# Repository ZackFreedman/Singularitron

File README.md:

# Singularitron
## Ridiculous VFD-equipped modular cyberwatch

More info at the [Singularitron's Hackaday.io page.](https://hackaday.io/project/169343-singularitron-modular-cyberwatch)

The Singularitron is a massive wrist-mounted wearable device with four expansion slots. Equip any combination of flashlight, laser, IR thermometer, environmental, and SD card modules, and stun the crowd with RGB buttons. The ultra-bright, extremely breakable VFD adds bright-daylight readability... and style.

Real talk, this does work, but is not intended to be a serious project. A VFD is a terrible choice for a wearable, and many parts of the project are suboptimal, ridiculous, and/or barely functional. Also, I made a bunch of boo-boos on the board and fixed them with airwires. I'll fix that some time, maybe.

That said, it serves its purpose - drawing attention at Meetups and conferences - really well. The cartridge form-factor is pretty cool, and this has neat super-small implementations of some interesting parts. Have fun!

If you really do want to build this, there are a lot of gotchas:

* I'll add them
* Eventually
* Right here

Copyright 2017 Zack Freedman

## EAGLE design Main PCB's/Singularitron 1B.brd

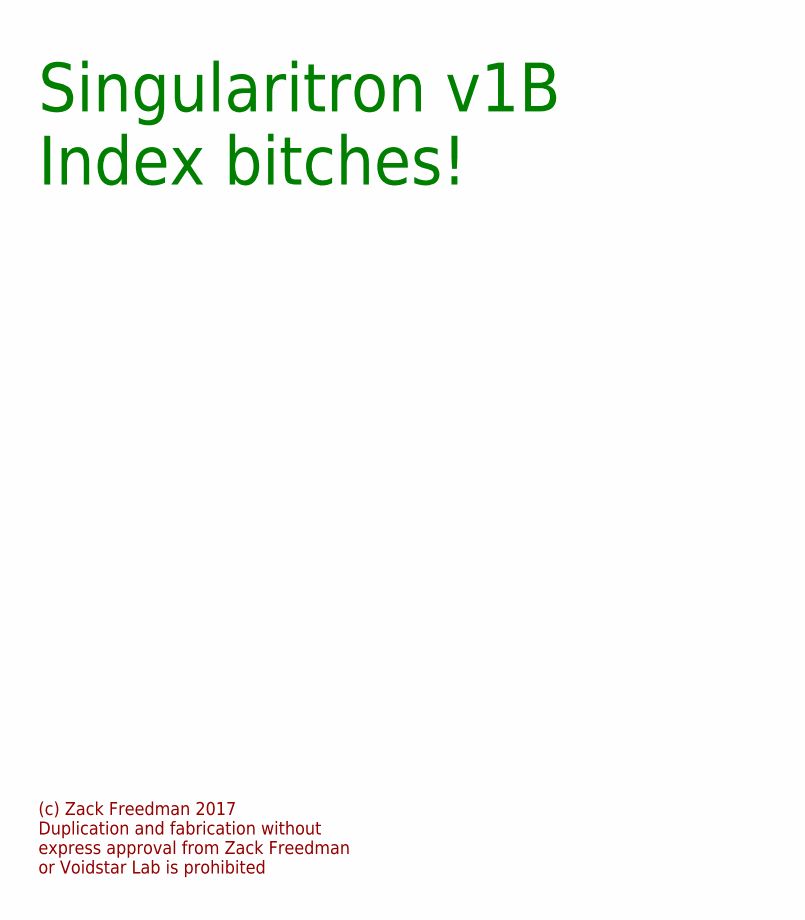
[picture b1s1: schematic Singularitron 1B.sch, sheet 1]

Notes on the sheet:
Singularitron v1B Index bitches!
(c) Zack Freedman 2017 Duplication and fabrication without express approval from Zack Freedman or Voidstar Lab is prohibited

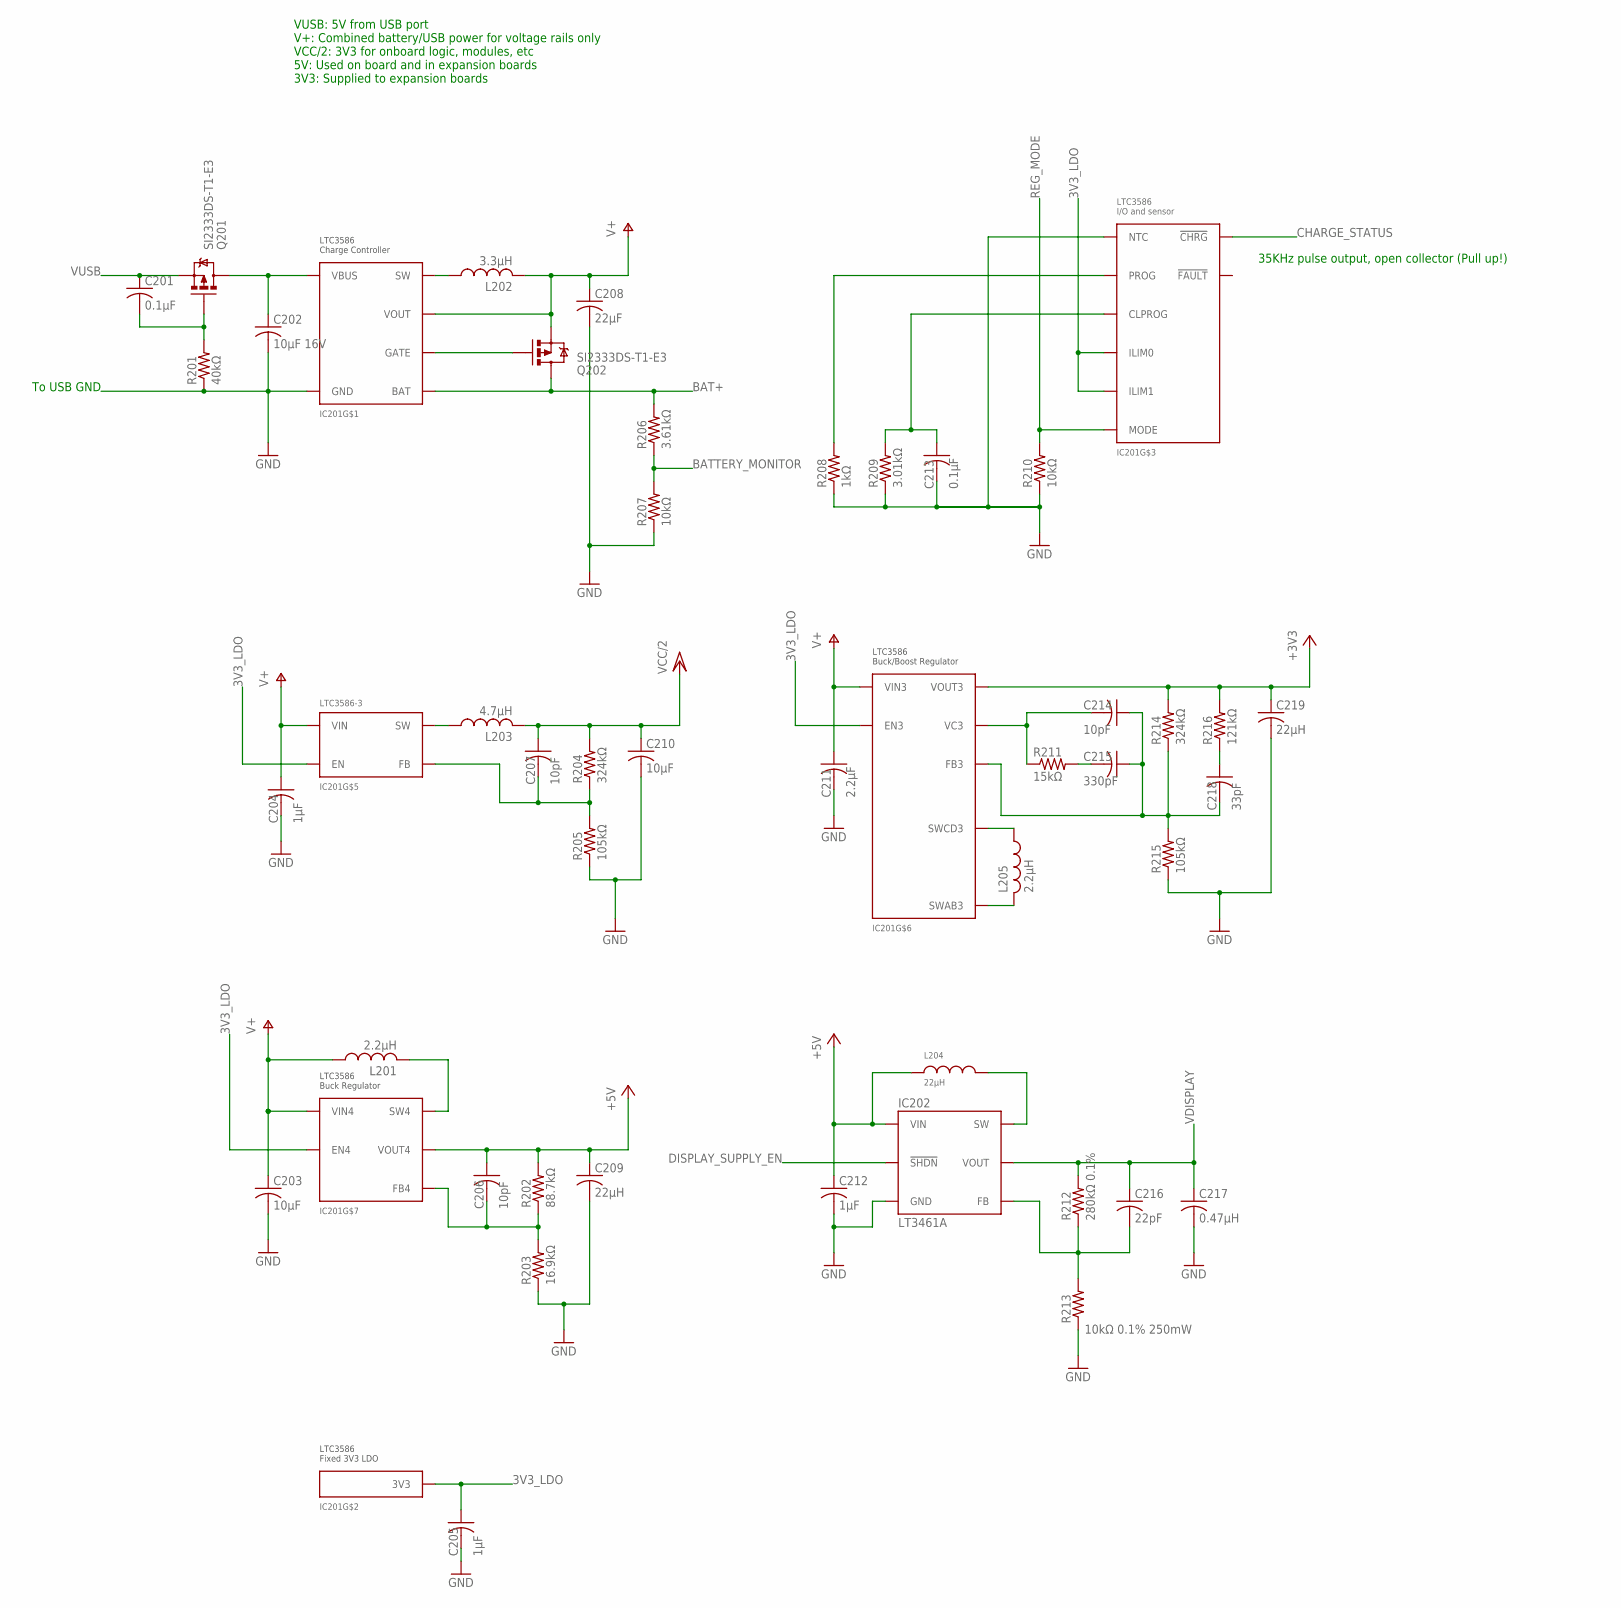
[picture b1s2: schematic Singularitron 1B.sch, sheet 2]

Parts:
C201, C213: 0.1µF; C0603
C202: 10µF 16V; C0805
C203, C210: 10µF; C0805
C204, C205: 1µF; C0603
C206, C207, C214: 10pF; C0603
C208: 22µF; C1210
C209, C219: 22µH; C1210
C211: 2.2µF; C0603
C212: 1µF; C0805
C215: 330pF; C0603
C216: 22pF; C0805
C217: 0.47µH; C1210
C218: 33pF; C0603
IC201: LTC3586-3; QFN-38_EP_UFE
IC202: LT3461A; SOT-23
L201, L205: 2.2µH; CDRH4D22/HP
L202: 3.3µH; CDRH6D12
L203: 4.7µH; CDRH3D16/HP
L204: 22µH; CDPH4D19F
Q201, Q202: SI2333DS-T1-E3; SOT23-3
R201: 40kΩ; R0603
R202: 88.7kΩ; R0603
R203: 16.9kΩ; R0603
R204, R214: 324kΩ; R0603
R205, R215: 105kΩ; R0603
R206: 3.61kΩ; R0603
R207, R210: 10kΩ; R0603
R208: 1kΩ; R0603
R209: 3.01kΩ; R0603
R211: 15kΩ; R0603
R212: 280kΩ 0.1%; R0603
R213: 10kΩ 0.1% 250mW; R0805
R216: 121kΩ; R0603

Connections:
3V3_LDO: C205.1, IC201.P$1 (ILIM0), IC201.P$2 (ILIM1), IC201.P$3 (3V3), IC201.P$18 (EN3), IC201.P$20 (EN), IC201.P$33 (EN4); also elsewhere on the board
+3V3: C219.1, IC201.P$16 (VOUT3), IC201.P$17 (VOUT3), R214.2, R216.2; also elsewhere on the board
+5V: C206.1, C209.1, C212.1, IC201.P$6 (VOUT4), IC201.P$7 (VOUT4), IC202.P6 (VIN), L204.P$1, R202.2; also elsewhere on the board
BAT+: IC201.P$32 (BAT), Q202.3 (D), R206.2; also elsewhere on the board
BATTERY_MONITOR: R206.1, R207.2; also elsewhere on the board
CHARGE_STATUS: IC201.P$30 (!CHRG); also elsewhere on the board
CLPROG: C213.1, IC201.P$4 (CLPROG), R209.2
DISPLAY_SUPPLY_EN: IC202.P4 (!SHDN); also elsewhere on the board
GND: C202.2, C203.2, C204.2, C205.2, C208.2, C209.2, C210.2, C211.2, C212.2, C213.2, C217.2, C219.2, IC201.EP (GND), IC201.P$5 (NTC), IC202.P2 (GND), R201.1, R203.1, R205.1, R207.1, R208.1, R209.1, R210.1, R213.1, R215.1; also elsewhere on the board
unnamed: C202.1, IC201.P$35 (VBUS), IC201.P$36 (VBUS), Q201.3 (D)
unnamed: IC201.P$37 (SW), L202.P$1 (1)
unnamed: C201.2, Q201.1 (G), R201.2
unnamed: IC201.P$31 (GATE), Q202.1 (G)
unnamed: IC201.P$25 (SW), L203.P$1 (1)
unnamed: IC201.P$29 (PROG), R208.2
unnamed: C207.2, IC201.P$23 (FB), R204.1, R205.2
unnamed: IC202.P1 (SW), L204.P$2
unnamed: C214.2, IC201.P$12 (VC3), R211.1
unnamed: C216.2, IC202.P3 (FB), R212.1, R213.2
unnamed: C215.2, R211.2
unnamed: IC201.P$8 (SW4), L201.P$2 (2)
unnamed: C218.1, R216.1
unnamed: C206.2, IC201.P$10 (FB4), R202.1, R203.2
unnamed: C214.1, C215.1, C218.2, IC201.P$11 (FB3), R214.1, R215.2
unnamed: IC201.P$19 (SWCD3), L205.P$1 (1)
unnamed: IC201.P$13 (SWAB3), L205.P$2 (2)
REG_MODE: IC201.P$9 (MODE), R210.2
V+: C203.1, C204.1, C208.1, C211.1, IC201.P$14 (VIN3), IC201.P$15 (VIN3), IC201.P$22 (VIN4), IC201.P$24 (VIN), IC201.P$34 (VOUT), L201.P$1 (1), L202.P$3 (2), Q202.2 (S)
VCC/2: C207.1, C210.1, L203.P$2 (2), R204.2; also elsewhere on the board
VDISPLAY: C216.1, C217.1, IC202.P5 (VOUT), R212.2; also elsewhere on the board
VUSB: C201.1, Q201.2 (S); also elsewhere on the board

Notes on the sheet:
To USB GND
VUSB: 5V from USB port V+: Combined battery/USB power for voltage rails only VCC/2: 3V3 for onboard logic, modules, etc 5V: Used on board and in expansion boards 3V3: Supplied to expansion boards
35KHz pulse output, open collector (Pull up!)

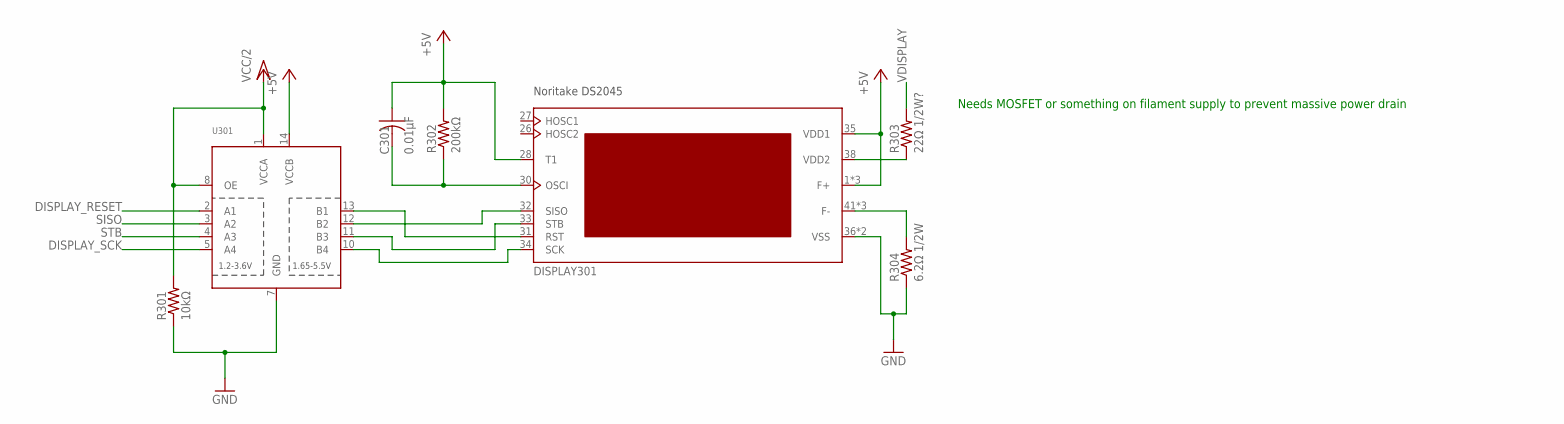
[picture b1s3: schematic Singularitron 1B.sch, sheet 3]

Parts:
C301: 0.01µF; C0603
DISPLAY301: DS2045
R301: 10kΩ; R0603
R302: 200kΩ; R0603
R303: 22Ω 1/2W?; R0805
R304: 6.2Ω 1/2W; R0805
U301: TXB0104PWR; TSSOP14

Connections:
+5V: C301.1, DISPLAY301.1 (F+), DISPLAY301.2 (F+), DISPLAY301.3 (F+), DISPLAY301.28 (T1), DISPLAY301.35 (VDD1), R302.2, U301.14 (VCCB); also elsewhere on the board
DISPLAY_RESET: U301.2 (A1); also elsewhere on the board
DISPLAY_SCK: U301.5 (A4); also elsewhere on the board
GND: DISPLAY301.36 (VSS), DISPLAY301.37 (VSS), R301.1, R304.1, U301.7 (GND); also elsewhere on the board
unnamed: DISPLAY301.31 (RST), U301.13 (B1)
unnamed: DISPLAY301.38 (VDD2), R303.1
unnamed: DISPLAY301.41 (F-), DISPLAY301.42 (F-), DISPLAY301.43 (F-), R304.2
unnamed: DISPLAY301.32 (SISO), U301.12 (B2)
unnamed: DISPLAY301.33 (STB), U301.11 (B3)
unnamed: DISPLAY301.34 (SCK), U301.10 (B4)
unnamed: C301.2, DISPLAY301.30 (OSCI), R302.1
SISO: U301.3 (A2); also elsewhere on the board
STB: U301.4 (A3); also elsewhere on the board
VCC/2: R301.2, U301.1 (VCCA), U301.8 (OE); also elsewhere on the board
VDISPLAY: R303.2; also elsewhere on the board

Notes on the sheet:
Needs MOSFET or something on filament supply to prevent massive power drain

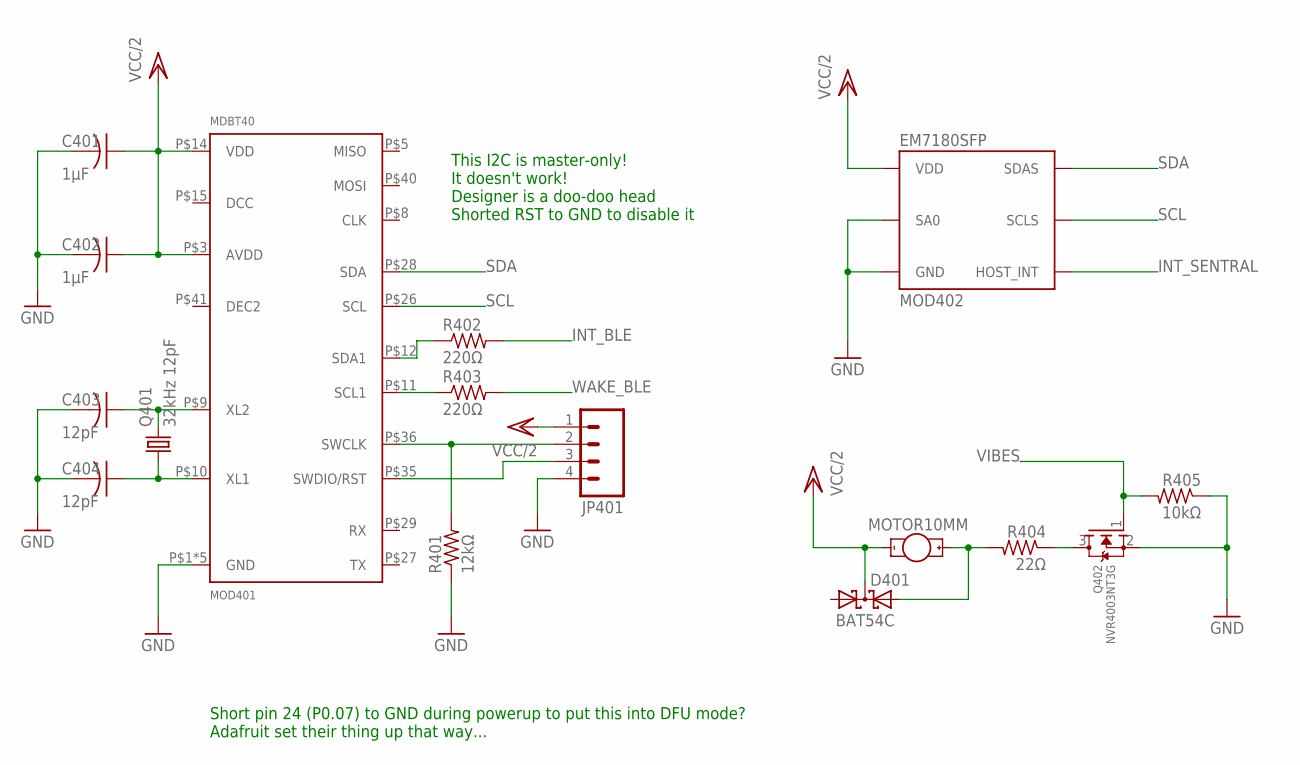
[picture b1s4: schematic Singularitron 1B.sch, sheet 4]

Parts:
C401, C402: 1µF; C0603
C403, C404: 12pF; C0603
D401: BAT54C; SOT23
JP401: M041.27MM; 1X04-1.27MM
MOD401: MDBT40
MOD402: EM7180SFP
MOTOR401: MOTOR10MM; VIBE-MOTOR-10MM
Q401: 32kHz 12pF; FC-12M
Q402: NVR4003NT3G; SOT23
R401: 12kΩ; R0603
R402, R403: 220Ω; R0603
R404: 22Ω; R0603
R405: 10kΩ; R0603

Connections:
GND: C401.2, C402.2, C403.2, C404.2, JP401.4, MOD401.P$1 (GND), MOD401.P$2 (GND), MOD401.P$13 (GND), MOD401.P$25 (GND), MOD401.P$42 (GND), MOD402.P$5 (SA0), MOD402.P$6 (GND), Q402.2 (S), R401.1, R405.1; also elsewhere on the board
INT_BLE: R402.2; also elsewhere on the board
INT_SENTRAL: MOD402.P$4 (HOST_INT); also elsewhere on the board
unnamed: MOD401.P$12 (SDA1), R402.1
unnamed: D401.2 (A2), MOTOR401.+, R404.2
unnamed: MOD401.P$11 (SCL1), R403.1
unnamed: Q402.3 (D), R404.1
unnamed: C404.1, MOD401.P$10 (XL1), Q401.1
unnamed: C403.1, MOD401.P$9 (XL2), Q401.2
unnamed: JP401.2, MOD401.P$36 (SWCLK), R401.2
unnamed: JP401.3, MOD401.P$35 (SWDIO/RST)
SCL: MOD401.P$26 (SCL), MOD402.P$3 (SCLS); also elsewhere on the board
SDA: MOD401.P$28 (SDA), MOD402.P$2 (SDAS); also elsewhere on the board
VCC/2: C401.1, C402.1, D401.3 (CC), JP401.1, MOD401.P$3 (AVDD), MOD401.P$14 (VDD), MOD402.P$1 (VDD), MOTOR401.-; also elsewhere on the board
VIBES: Q402.1 (G), R405.2; also elsewhere on the board
WAKE_BLE: R403.2; also elsewhere on the board

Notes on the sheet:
This I2C is master-only! It doesn't work! Designer is a doo-doo head Shorted RST to GND to disable it
Short pin 24 (P0.07) to GND during powerup to put this into DFU mode? Adafruit set their thing up that way...

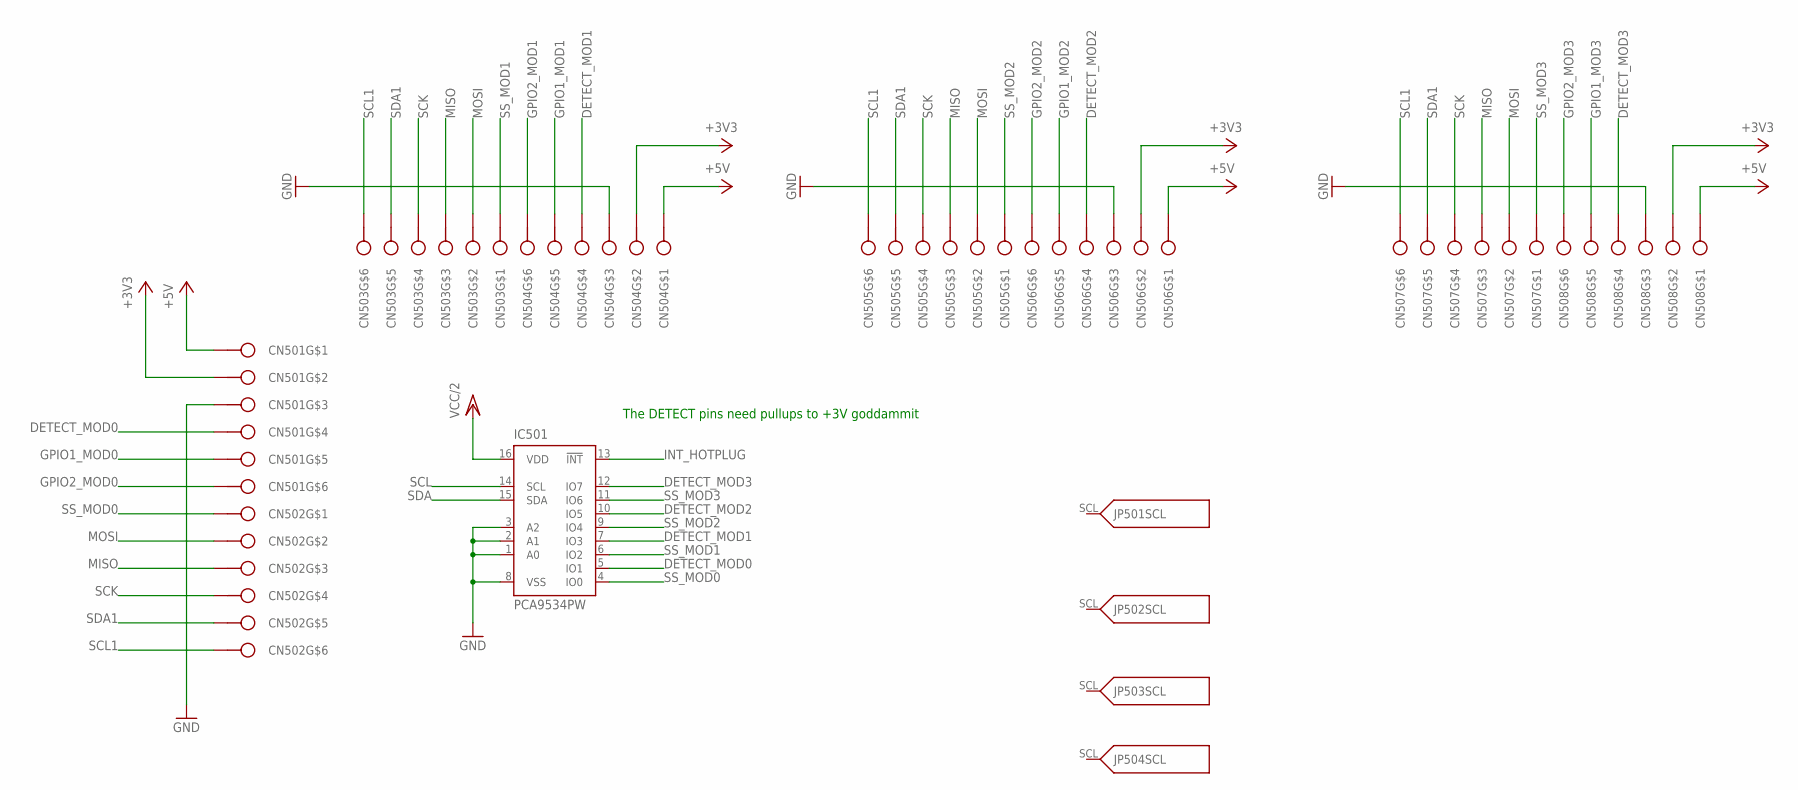
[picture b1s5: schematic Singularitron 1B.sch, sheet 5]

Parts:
CN501, CN502, CN503, CN504, CN505, CN506, CN507, CN508: AVX_9155066; 9155006
IC501: PCA9534PW; TSSOP16
JP501, JP502, JP503, JP504: SINGULARITRON_CART_BASE

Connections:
+3V3: CN501.PAD2, CN504.PAD2, CN506.PAD2, CN508.PAD2; also elsewhere on the board
+5V: CN501.PAD1, CN504.PAD1, CN506.PAD1, CN508.PAD1; also elsewhere on the board
DETECT_MOD0: CN501.PAD4, IC501.5 (IO1)
DETECT_MOD1: CN504.PAD4, IC501.7 (IO3)
DETECT_MOD2: CN506.PAD4, IC501.10 (IO5)
DETECT_MOD3: CN508.PAD4, IC501.12 (IO7)
GND: CN501.PAD3, CN504.PAD3, CN506.PAD3, CN508.PAD3, IC501.1 (A0), IC501.2 (A1), IC501.3 (A2), IC501.8 (VSS); also elsewhere on the board
GPIO1_MOD0: CN501.PAD5; also elsewhere on the board
GPIO1_MOD1: CN504.PAD5; also elsewhere on the board
GPIO1_MOD2: CN506.PAD5; also elsewhere on the board
GPIO1_MOD3: CN508.PAD5; also elsewhere on the board
GPIO2_MOD0: CN501.PAD6; also elsewhere on the board
GPIO2_MOD1: CN504.PAD6; also elsewhere on the board
GPIO2_MOD2: CN506.PAD6; also elsewhere on the board
GPIO2_MOD3: CN508.PAD6; also elsewhere on the board
INT_HOTPLUG: IC501.13 (!INT); also elsewhere on the board
MISO: CN502.PAD3, CN503.PAD3, CN505.PAD3, CN507.PAD3; also elsewhere on the board
MOSI: CN502.PAD2, CN503.PAD2, CN505.PAD2, CN507.PAD2; also elsewhere on the board
SCK: CN502.PAD4, CN503.PAD4, CN505.PAD4, CN507.PAD4; also elsewhere on the board
SCL: IC501.14 (SCL); also elsewhere on the board
SCL1: CN502.PAD6, CN503.PAD6, CN505.PAD6, CN507.PAD6; also elsewhere on the board
SDA: IC501.15 (SDA); also elsewhere on the board
SDA1: CN502.PAD5, CN503.PAD5, CN505.PAD5, CN507.PAD5; also elsewhere on the board
SS_MOD0: CN502.PAD1, IC501.4 (IO0)
SS_MOD1: CN503.PAD1, IC501.6 (IO2)
SS_MOD2: CN505.PAD1, IC501.9 (IO4)
SS_MOD3: CN507.PAD1, IC501.11 (IO6)
VCC/2: IC501.16 (VDD); also elsewhere on the board

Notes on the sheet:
The DETECT pins need pullups to +3V goddammit

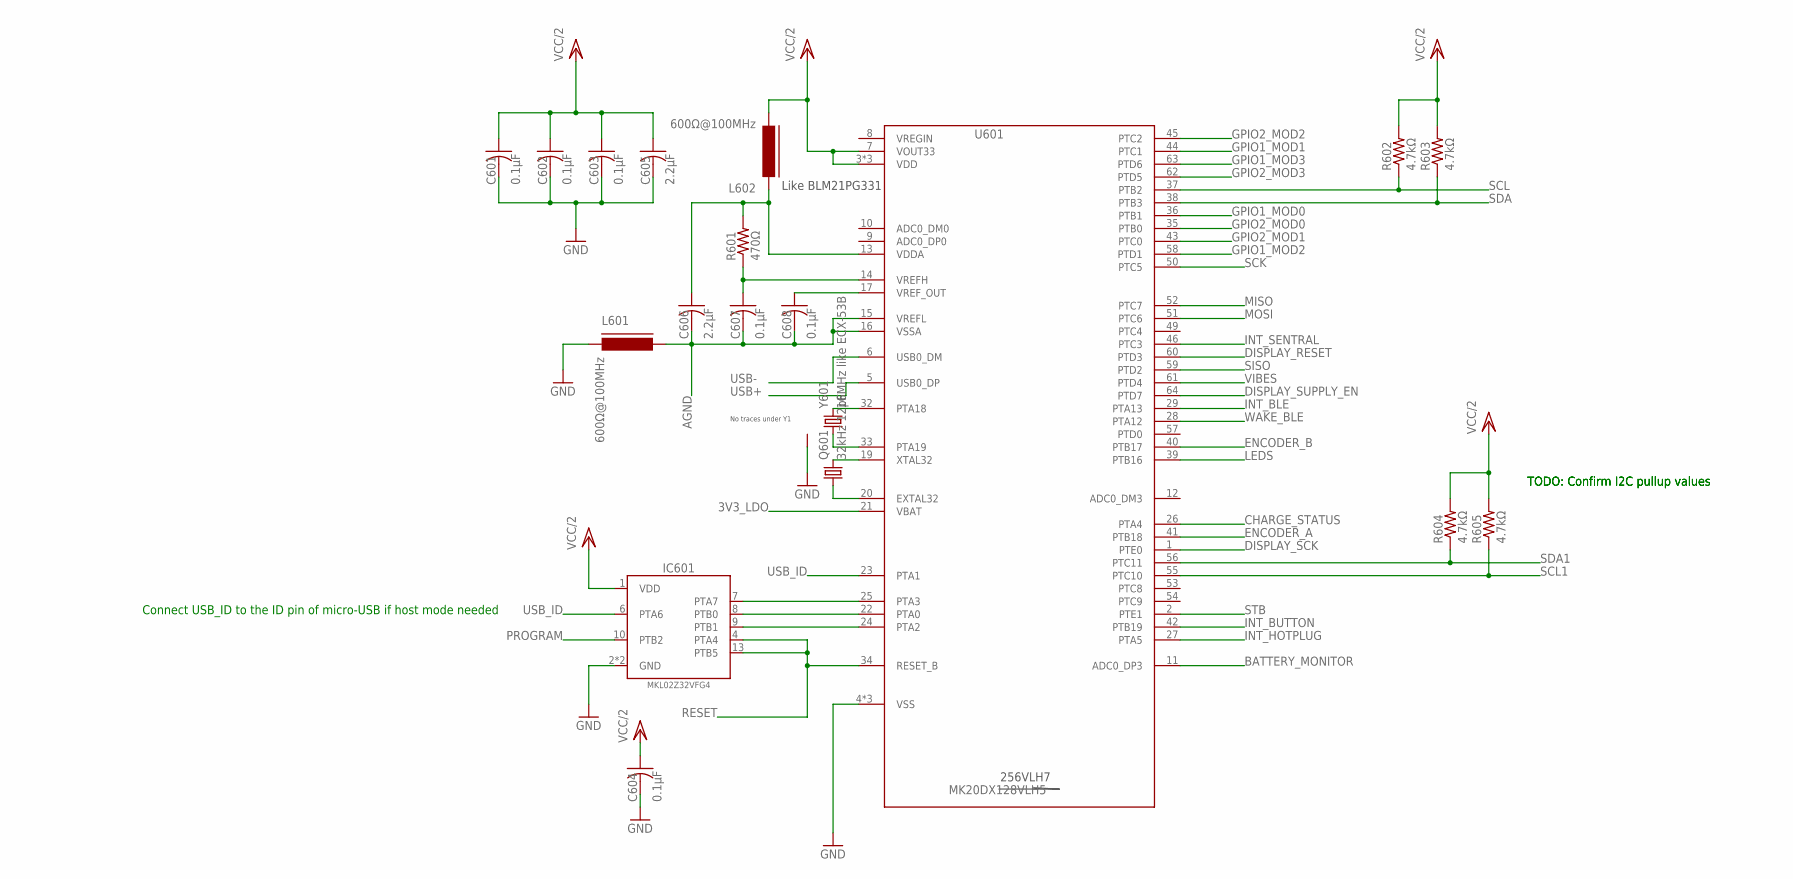
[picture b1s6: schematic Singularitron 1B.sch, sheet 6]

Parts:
C601, C602, C603, C604, C607, C608: 0.1µF; C0603
C605, C606: 2.2µF; C0603
IC601: MKL02Z32VFG4; QFN16-3X3
L601, L602: 600Ω@100MHz; FB603
Q601: 32kHz 12pF; FC-12M
R601: 470Ω; R0603
R602, R603, R604, R605: 4.7kΩ; R0603
U601: MK20DX128VLH5
Y601: 16MHz like ECX-53B; CRYSTAL-SMD-5X3

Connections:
3V3_LDO: U601.21 (VBAT); also elsewhere on the board
AGND: C606.2, C607.2, C608.2, L601.1, U601.15 (VREFL), U601.16 (VSSA)
BATTERY_MONITOR: U601.11 (ADC0_DP3); also elsewhere on the board
CHARGE_STATUS: U601.26 (PTA4); also elsewhere on the board
DISPLAY_RESET: U601.60 (PTD3); also elsewhere on the board
DISPLAY_SCK: U601.1 (PTE0); also elsewhere on the board
DISPLAY_SUPPLY_EN: U601.64 (PTD7); also elsewhere on the board
ENCODER_A: U601.41 (PTB18); also elsewhere on the board
ENCODER_B: U601.40 (PTB17); also elsewhere on the board
GND: C601.2, C602.2, C603.2, C604.2, C605.2, IC601.2 (GND), IC601.PAD (GND), L601.2, U601.4 (VSS), U601.31 (VSS), U601.47 (VSS), Y601.2 (SHIELD), Y601.4 (SHIELD); also elsewhere on the board
GPIO1_MOD0: U601.36 (PTB1); also elsewhere on the board
GPIO1_MOD1: U601.44 (PTC1); also elsewhere on the board
GPIO1_MOD2: U601.58 (PTD1); also elsewhere on the board
GPIO1_MOD3: U601.63 (PTD6); also elsewhere on the board
GPIO2_MOD0: U601.35 (PTB0); also elsewhere on the board
GPIO2_MOD1: U601.43 (PTC0); also elsewhere on the board
GPIO2_MOD2: U601.45 (PTC2); also elsewhere on the board
GPIO2_MOD3: U601.62 (PTD5); also elsewhere on the board
INT_BLE: U601.29 (PTA13); also elsewhere on the board
INT_BUTTON: U601.42 (PTB19); also elsewhere on the board
INT_HOTPLUG: U601.27 (PTA5); also elsewhere on the board
INT_SENTRAL: U601.46 (PTC3); also elsewhere on the board
LEDS: U601.39 (PTB16); also elsewhere on the board
MISO: U601.52 (PTC7); also elsewhere on the board
MOSI: U601.51 (PTC6); also elsewhere on the board
unnamed: IC601.7 (PTA7), U601.25 (PTA3)
unnamed: IC601.8 (PTB0), U601.22 (PTA0)
unnamed: IC601.9 (PTB1), U601.24 (PTA2)
unnamed: U601.32 (PTA18), Y601.3 (2)
unnamed: U601.33 (PTA19), Y601.1
unnamed: Q601.2, U601.19 (XTAL32)
unnamed: Q601.1, U601.20 (EXTAL32)
unnamed: C608.1, U601.17 (VREF_OUT)
unnamed: C607.1, R601.1, U601.14 (VREFH)
unnamed: C606.1, L602.1, R601.2, U601.13 (VDDA)
PROGRAM: IC601.10 (PTB2); also elsewhere on the board
RESET: IC601.4 (PTA4), IC601.13 (PTB5), U601.34 (RESET_B)
SCK: U601.50 (PTC5); also elsewhere on the board
SCL: R602.1, U601.37 (PTB2); also elsewhere on the board
SCL1: R605.1, U601.55 (PTC10); also elsewhere on the board
SDA: R603.1, U601.38 (PTB3); also elsewhere on the board
SDA1: R604.1, U601.56 (PTC11); also elsewhere on the board
SISO: U601.59 (PTD2); also elsewhere on the board
STB: U601.2 (PTE1); also elsewhere on the board
USB+: U601.5 (USB0_DP); also elsewhere on the board
USB-: U601.6 (USB0_DM); also elsewhere on the board
USB_ID: IC601.6 (PTA6), U601.23 (PTA1)
VCC/2: C601.1, C602.1, C603.1, C604.1, C605.1, IC601.1 (VDD), L602.2, R602.2, R603.2, R604.2, R605.2, U601.3 (VDD), U601.7 (VOUT33), U601.30 (VDD), U601.48 (VDD); also elsewhere on the board
VIBES: U601.61 (PTD4); also elsewhere on the board
WAKE_BLE: U601.28 (PTA12); also elsewhere on the board

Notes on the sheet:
256VLH7
Like BLM21PG331
No traces under Y1
Connect USB_ID to the ID pin of micro-USB if host mode needed
TODO: Confirm I2C pullup values

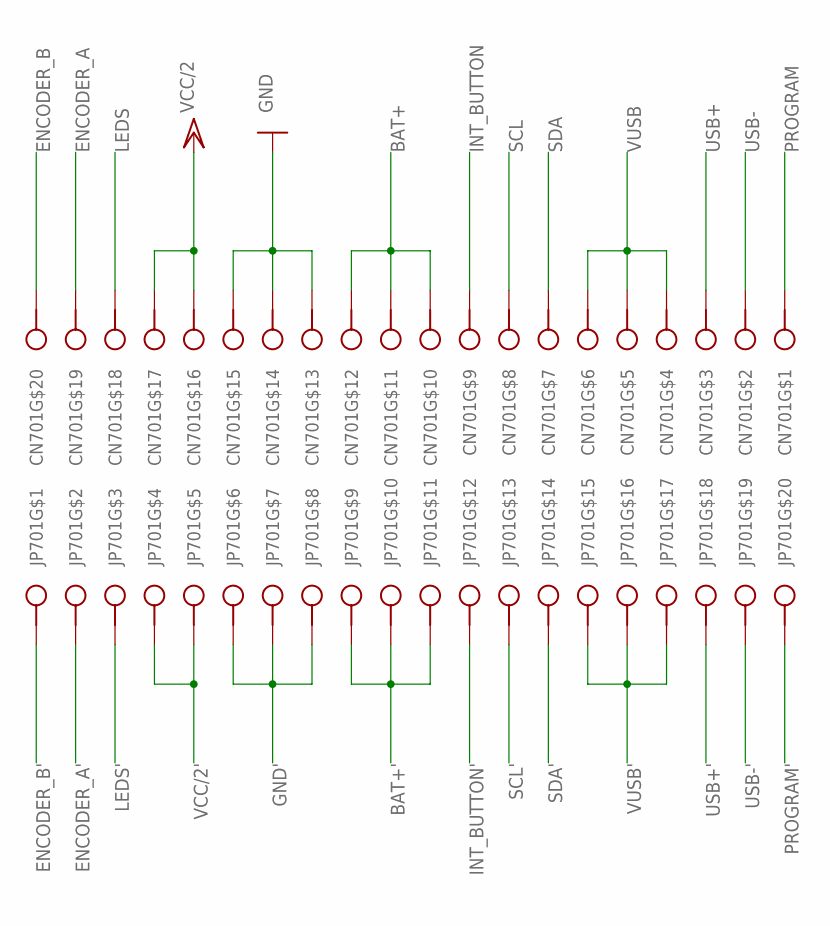
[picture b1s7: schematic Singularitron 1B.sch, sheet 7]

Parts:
CN701: HFW20R-1ST; HFW20R-1STE1LF
JP701: FFC_1MM_20POS_DIRECT

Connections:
BAT+: CN701.P$10, CN701.P$11, CN701.P$12; also elsewhere on the board
BAT+': JP701.P$9, JP701.P$10, JP701.P$11; also elsewhere on the board
ENCODER_A: CN701.P$19; also elsewhere on the board
ENCODER_A': JP701.P$2; also elsewhere on the board
ENCODER_B: CN701.P$20; also elsewhere on the board
ENCODER_B': JP701.P$1; also elsewhere on the board
GND: CN701.P$13, CN701.P$14, CN701.P$15; also elsewhere on the board
GND': JP701.P$6, JP701.P$7, JP701.P$8; also elsewhere on the board
INT_BUTTON: CN701.P$9; also elsewhere on the board
INT_BUTTON': JP701.P$12; also elsewhere on the board
LEDS: CN701.P$18; also elsewhere on the board
LEDS': JP701.P$3; also elsewhere on the board
PROGRAM: CN701.P$1; also elsewhere on the board
PROGRAM': JP701.P$20; also elsewhere on the board
SCL: CN701.P$8; also elsewhere on the board
SCL': JP701.P$13; also elsewhere on the board
SDA: CN701.P$7; also elsewhere on the board
SDA': JP701.P$14; also elsewhere on the board
USB+: CN701.P$3; also elsewhere on the board
USB+': JP701.P$18; also elsewhere on the board
USB-: CN701.P$2; also elsewhere on the board
USB-': JP701.P$19; also elsewhere on the board
VCC/2: CN701.P$16, CN701.P$17; also elsewhere on the board
VCC/2': JP701.P$4, JP701.P$5; also elsewhere on the board
VUSB: CN701.P$4, CN701.P$5, CN701.P$6; also elsewhere on the board
VUSB': JP701.P$15, JP701.P$16, JP701.P$17; also elsewhere on the board

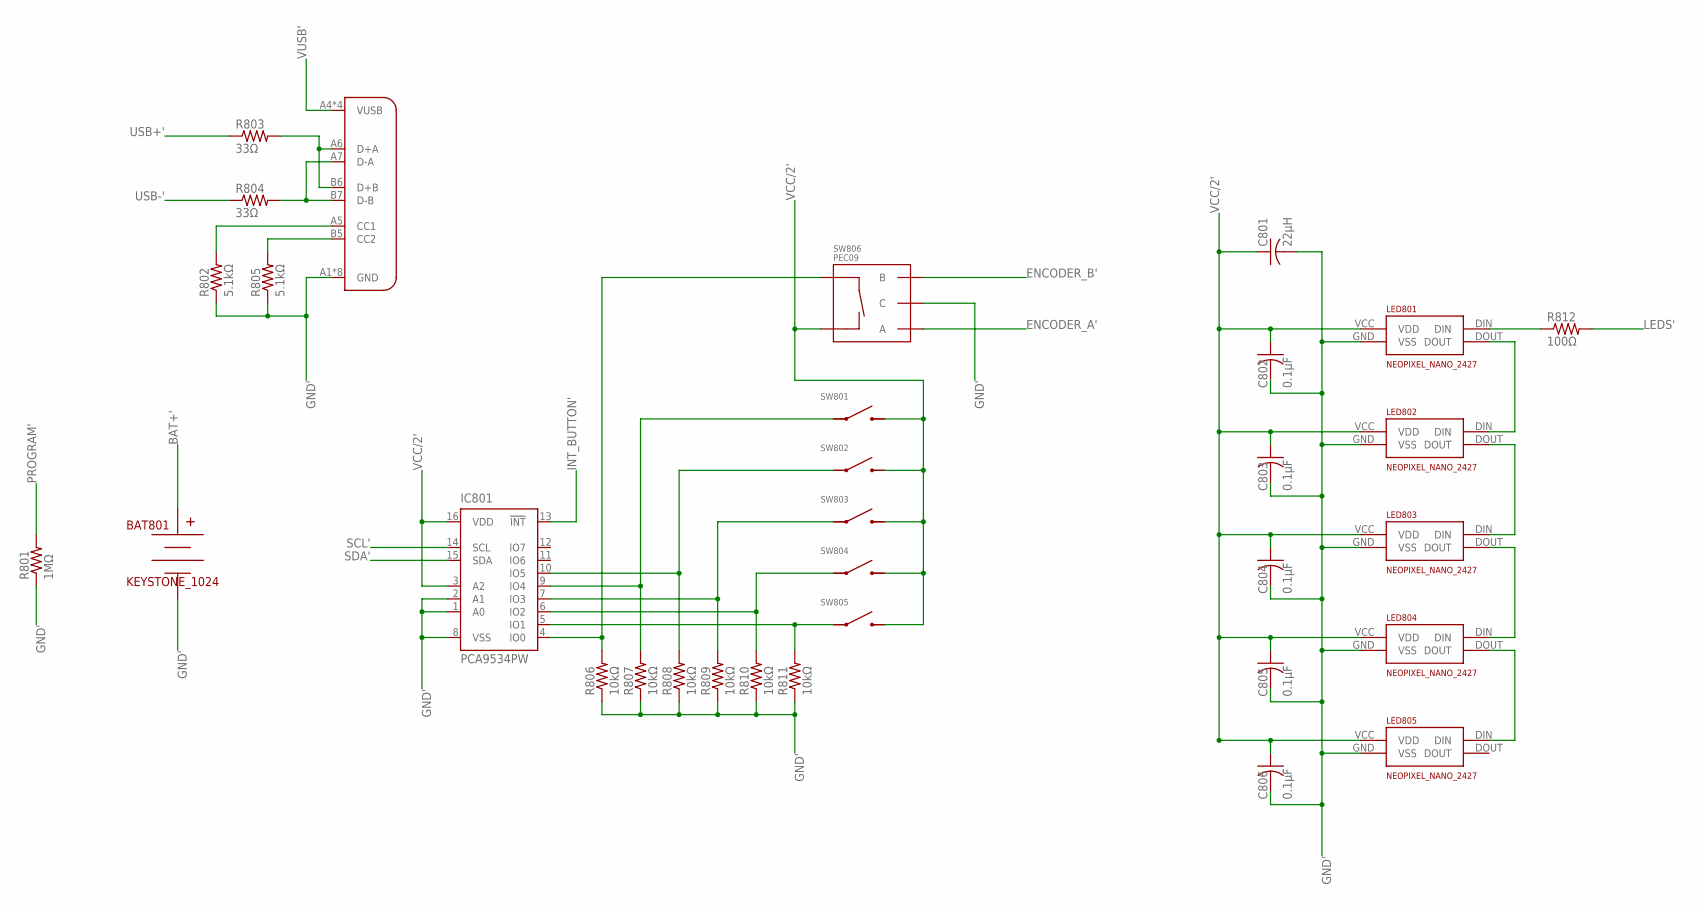
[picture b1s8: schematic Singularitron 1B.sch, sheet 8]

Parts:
BAT801: KEYSTONE_1024; KEYSTONE-1024-PROVISIONAL
C801: 22µH; C1210
C802, C803, C804, C805, C806: 0.1µF; C0603
CN801: 12401548E4#2A
IC801: PCA9534PW; TSSOP16
LED801, LED802, LED803, LED804, LED805: NEOPIXEL_NANO_2427; SK6805-2427
R801: 1MΩ; R0603
R802, R805: 5.1kΩ; R0603
R803, R804: 33Ω; R0603
R806, R807, R808, R809, R810, R811: 10kΩ; R0603
R812: 100Ω; R0603
SW801, SW802, SW803, SW804, SW805: TACTILE_SWITCHTL3301-G; TL3301-X-FXXX-X-G
SW806: PEC09; PEC09-2X20X-TXXXX

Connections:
BAT+': BAT801.+ (V+); also elsewhere on the board
ENCODER_A': SW806.A; also elsewhere on the board
ENCODER_B': SW806.B; also elsewhere on the board
GND': BAT801.- (V-), C801.2, C802.2, C803.2, C804.2, C805.2, C806.2, CN801.A1 (GND), CN801.A12 (GND), CN801.B1 (GND), CN801.B12 (GND), CN801.SHIELD1 (GND), CN801.SHIELD2 (GND), CN801.SHIELD3 (GND), CN801.SHIELD4 (GND), IC801.1 (A0), IC801.2 (A1), IC801.8 (VSS), LED801.GND (VSS), LED802.GND (VSS), LED803.GND (VSS), LED804.GND (VSS), LED805.GND (VSS), R801.1, R802.1, R805.1, R806.1, R807.1, R808.1, R809.1, R810.1, R811.1, SW806.C; also elsewhere on the board
INT_BUTTON': IC801.13 (!INT); also elsewhere on the board
LEDS': R812.2; also elsewhere on the board
unnamed: CN801.A6 (D+A), CN801.B6 (D+B), R803.2
unnamed: IC801.5 (IO1), R811.2, SW805.P$1, SW805.P$2
unnamed: IC801.6 (IO2), R810.2, SW804.P$1, SW804.P$2
unnamed: IC801.7 (IO3), R809.2, SW803.P$1, SW803.P$2
unnamed: CN801.A7 (D-A), CN801.B7 (D-B), R804.2
unnamed: IC801.10 (IO5), R808.2, SW802.P$1, SW802.P$2
unnamed: IC801.9 (IO4), R807.2, SW801.P$1, SW801.P$2
unnamed: LED801.DOUT, LED802.DIN
unnamed: LED802.DOUT, LED803.DIN
unnamed: LED803.DOUT, LED804.DIN
unnamed: LED804.DOUT, LED805.DIN
unnamed: LED801.DIN, R812.1
unnamed: IC801.4 (IO0), R806.2, SW806.D (SW+)
unnamed: CN801.A5 (CC1), R802.2
unnamed: CN801.B5 (CC2), R805.2
PROGRAM': R801.2; also elsewhere on the board
SCL': IC801.14 (SCL); also elsewhere on the board
SDA': IC801.15 (SDA); also elsewhere on the board
USB+': R803.1; also elsewhere on the board
USB-': R804.1; also elsewhere on the board
VCC/2': C801.1, C802.1, C803.1, C804.1, C805.1, C806.1, IC801.3 (A2), IC801.16 (VDD), LED801.VCC (VDD), LED802.VCC (VDD), LED803.VCC (VDD), LED804.VCC (VDD), LED805.VCC (VDD), SW801.P$3, SW801.P$4, SW802.P$3, SW802.P$4, SW803.P$3, SW803.P$4, SW804.P$3, SW804.P$4, SW805.P$3, SW805.P$4, SW806.E (SW-); also elsewhere on the board
VUSB': CN801.A4 (VUSB), CN801.A9 (VUSB), CN801.B4 (VUSB), CN801.B9 (VUSB); also elsewhere on the board

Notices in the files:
parts and their libraries:
SparkFun-DigitalIC: Licensing: CC v3.0 Share-Alike You are welcome to use this library for commercial purposes.
